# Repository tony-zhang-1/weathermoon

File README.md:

# Weathermoon
Multi-LED IoT Project for 3D Printed Moon (with optional sensor inputs)

This project develops a shield for the Wemos D1 Mini which has:

 -- 3 LEDs (White, Warm White, and RGB - Common Cathode).

 -- One (1) 3-Pin connector (D8)
 
 -- One (1) 4-Pin connector (A0, D0)

The 3-Pin connector will be used for a DH11 or similar humidity and temperature module. 

The 4-Pin connector will be used for a battery monitoring/control circuit, or another analog device.

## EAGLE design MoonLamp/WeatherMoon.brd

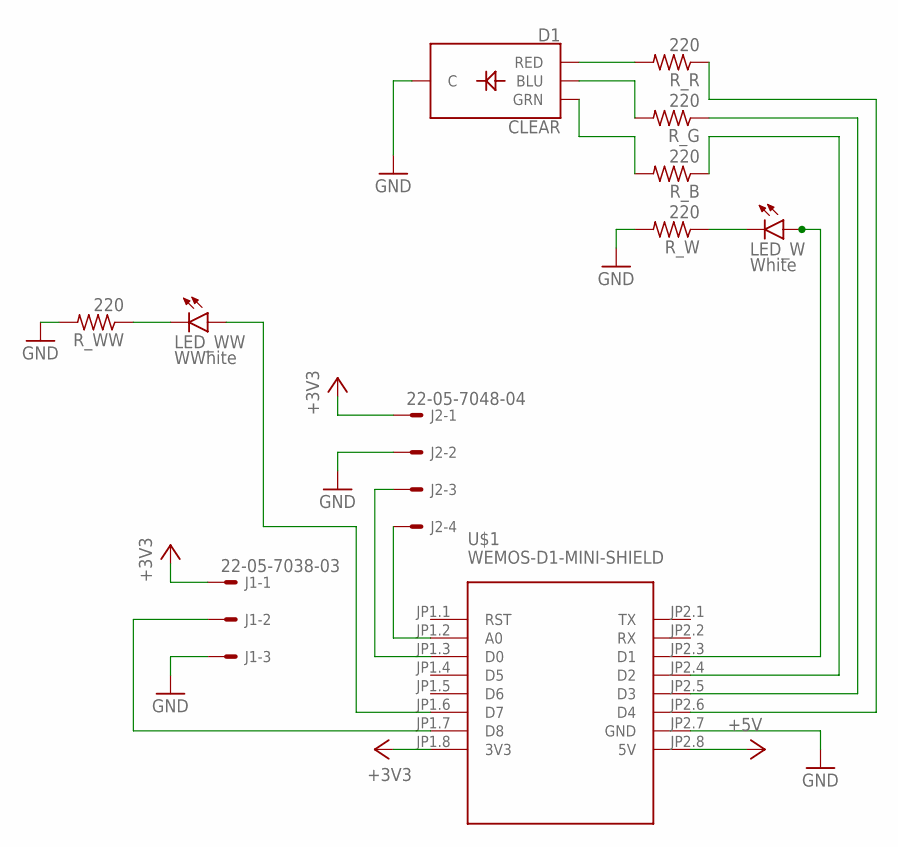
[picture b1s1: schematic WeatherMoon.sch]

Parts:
D1: CLEAR; LED-RGB-THRU
J1: 22-05-7038-03; 7395-03
J2: 22-05-7048-04; 7395-04
LED_W: White; LED5MM
LED_WW: WWhite; LED5MM
R_B: 220; 0204/7
R_G: 220; 0204/7
R_R: 220; 0204/7
R_W: 220; 0204/7
R_WW: 220; 0204/7
U$1: WEMOS-D1-MINI-SHIELD

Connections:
+3V3: J1.1, J2.1, U$1.JP1.8 (3V3)
+5V: U$1.JP2.8 (5V)
GND: D1.2 (C), J1.3, J2.2, R_W.2, R_WW.2, U$1.JP2.7 (GND)
unnamed: R_R.1, U$1.JP2.6 (D4)
unnamed: R_G.1, U$1.JP2.5 (D3)
unnamed: R_B.1, U$1.JP2.4 (D2)
unnamed: LED_W.A, U$1.JP2.3 (D1)
unnamed: LED_W.K (C), R_W.1
unnamed: D1.1 (RED), R_R.2
unnamed: D1.4 (BLU), R_G.2
unnamed: D1.3 (GRN), R_B.2
unnamed: LED_WW.A, U$1.JP1.6 (D7)
unnamed: J1.2, U$1.JP1.7 (D8)
unnamed: LED_WW.K (C), R_WW.1
unnamed: J2.4, U$1.JP1.2 (A0)
unnamed: J2.3, U$1.JP1.3 (D0)

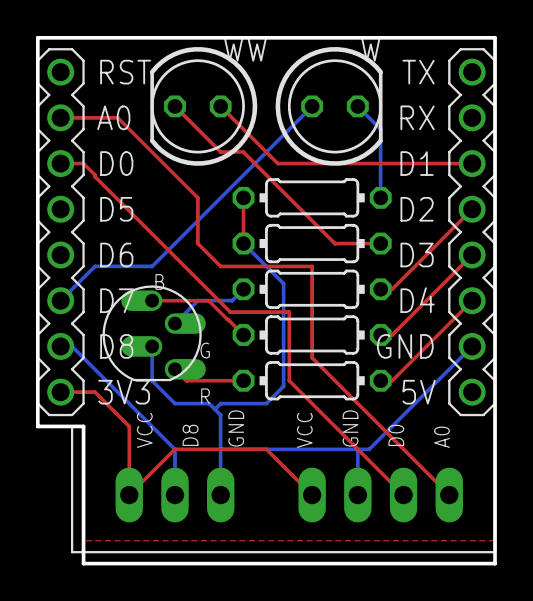
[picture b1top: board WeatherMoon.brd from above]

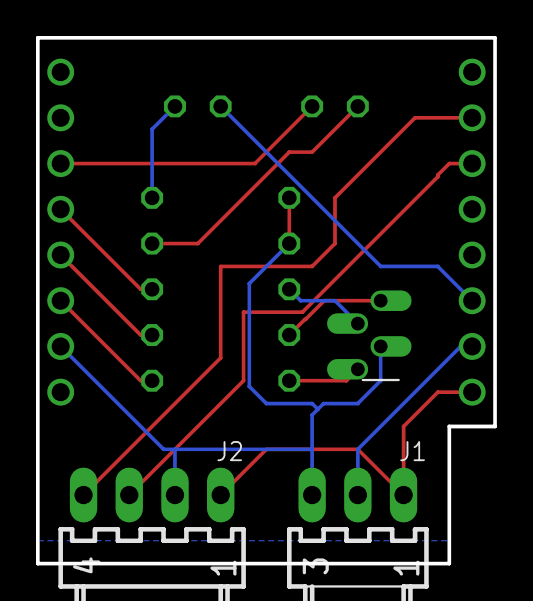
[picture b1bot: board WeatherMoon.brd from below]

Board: 2 copper layers, 25.4 x 29.2 mm, 11 parts (2 on the bottom side), 15 nets.

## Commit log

2021-01-30 Backup of Eagle Project
    Developed in Eagle. Contains Gerber exports for OshPark build
2021-01-31 Arduino Code

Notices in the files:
parts and their libraries:
SparkFun-LED: Licensing: Creative Commons ShareAlike 4.0 International - https://creativecommons.org/licenses/by-sa/4.0
diy-modules: Released under the Creative Commons Attribution 4.0 International License: http://creativecommons.org/licenses/by/4.0
